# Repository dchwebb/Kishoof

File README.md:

# Kishoof

## Overview

Kishoof is a Wavetable synthesizer designed for use in a Eurorack modular system. A dual channel architecture allows simultaneous playback of two channels each offering a different range of capabilities. Wavetables are held in 64MB of internal flash storage which is exposed as a USB disk drive via a front-panel USB C connector.

Two modes of operation are available with one stepping between individual wavetable frames and one smoothly interpolating between frames. In stepped mode channel A and B can each play any of the available wavetable frames. In smooth mode Channel A plays the loaded wavetable and channel B plays an internal wavetable that can be configured to hold a range of standard waveforms and harmonics.

A warp engine allows a range of warping effects to alter channel A's signal, with Bend, Squeeze, Mirror and though-Zero Frequency Modulation from channel B available. Channel B can be modulated via addition (mixing) and multiplication (ring modulation) with channel A and its playback direction can be reversed. Dynamic anti-aliasing filters eliminate aliasing regardless of modulation settings. 

A circular TFT LCD display shows both or either channel's waveform with any warping and modulation applied. A serial console available over a USB virtual COM port allows advanced configuration, calibration and trouble-shooting facilities.

The module was designed in conjunction with musician Tal Shoshani who produced the following demonstration video:

- **[Operation Manual](Kishoof_Manual.md)**

## Technical

Kishoof is based on an STM32H7B0 microcontroller clocked at 280MHz. Internal flash storage uses a Macronix MX25LM51245G 512Mbit NOR flash IC, clocked at 76.8MHz. The flash is controlled by the MCU using OctoSPI.

A TI PCM5100APW audio DAC is used for wavetable playback, operating in stereo at 48KHz. This is interfaced to the MCU over I2S. The MCU's internal 12 bit ADCs receive potentiometer and scaled Control voltage inputs.

The display is a circular 1.28 inch 240x240 IPS TFT LCD with GC9A01 Driver and is controlled via SPI. USB is connected via a front-panel USB C connector with ESD Protection.

**Construction**

The module is constructed of four PCBs: Component board, Control board, LCD daughterboard and Front Panel. The Component board is a 4-layer board. All others are 2 layer.

Circuit Design and layout using Kicad v8:

[Components schematic](Hardware/Kishoof_Components.pdf)

[Controls schematic](Hardware/Kishoof_Controls.pdf)

**Firmware**

Firmware written in C++20 using STM32CubeIDE version 1.15.1 and is available [here](Kishoof)

## Power

Digital power is supplied through a TI TPS561201 3.3V switching power supply and analog power via a 3.3V linear regulator.

- +12V current draw: 149 mA
- -12V Current draw: 7 mA

## Hardware Errata and Potential fixes

- VCA input should be normalised to a ~7V signal (currently bodged to 3.3V).
- Improve ground return paths on LCD daughterboard
- Invert LCD daughterboard to make orientation easier, and move pads towards cutout
- Fix footprint for switched potentiometer (Warp Type)

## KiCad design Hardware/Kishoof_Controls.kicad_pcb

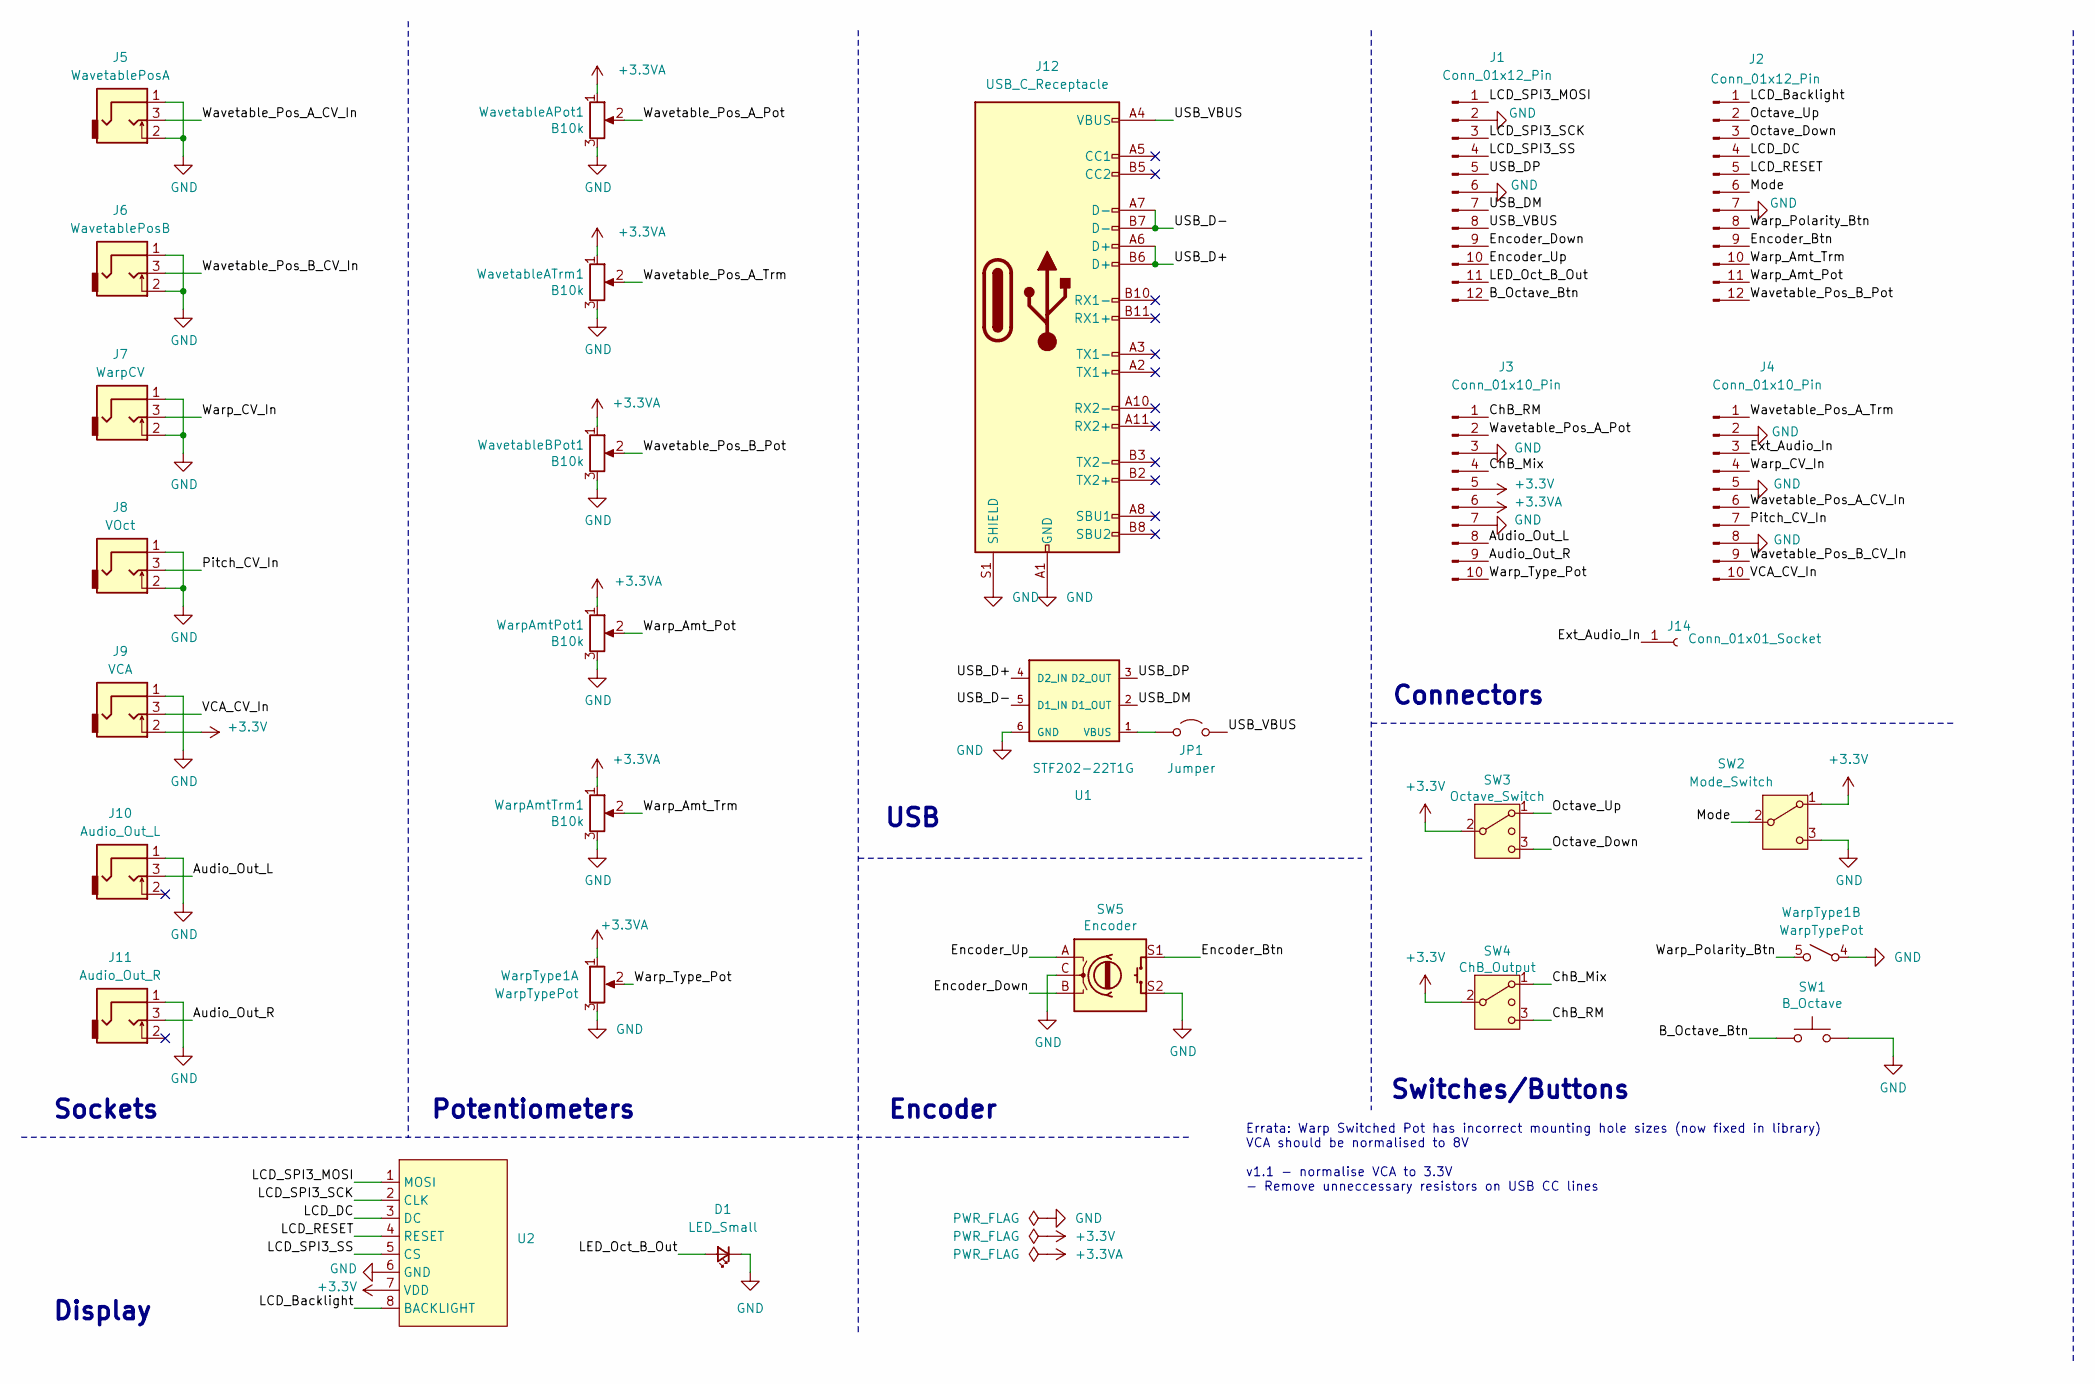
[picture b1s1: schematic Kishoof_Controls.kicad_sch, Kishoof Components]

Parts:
D1: LED_Small; LED_D3.0mm_FlatTop
J1, J2: Conn_01x12_Pin; PinSocket_1x12_P2.54mm_Vertical
J3, J4: Conn_01x10_Pin; PinSocket_1x10_P2.54mm_Vertical
J5: WavetablePosA; THONKICONN_hole
J6: WavetablePosB; THONKICONN_hole
J7: WarpCV; THONKICONN_hole
J8: VOct; THONKICONN_hole
J9: VCA; THONKICONN_hole
J10: Audio_Out_L; THONKICONN_hole
J11: Audio_Out_R; THONKICONN_hole
J12: USB_C_Receptacle; USB_C_Receptacle_Amphenol_12401951E412A
J14: Conn_01x01_Socket; PinHeader_1x01_P2.54mm_Vertical
JP1: Jumper; SolderJumper-2_P1.3mm_Open_RoundedPad1.0x1.5mm
SW1: B_Octave; SW_PUSH_6mm_aligned
SW2: Mode_Switch; SPDT_Miniature
SW3: Octave_Switch; SP3T_Mini_Switch
SW4: ChB_Output; SP3T_Mini_Switch
SW5: Encoder
U1: STF202-22T1G
U2: LCD_Riser
WarpAmtPot1: B10k; Alpha_9mm_Potentiometer_Aligned
WarpAmtTrm1: B10k; Alpha_9mm_Potentiometer_Aligned
WarpType1: WarpTypePot; Bourns_Switch_Potentiometer
WavetableAPot1: B10k; Alpha_9mm_Potentiometer_Aligned
WavetableATrm1: B10k; Alpha_9mm_Potentiometer_Aligned
WavetableBPot1: B10k; Alpha_9mm_Potentiometer_Aligned

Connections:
+3.3V: J3.5, J9.2, SW2.1 (A), SW3.2 (3), SW4.2 (3), U2.7 (VDD)
+3.3VA: J3.6, WarpAmtPot1.1, WarpAmtTrm1.1, WarpType1.1, WavetableAPot1.1, WavetableATrm1.1, WavetableBPot1.1
/Audio_Out_L: J3.8, J10.3
/Audio_Out_R: J3.9, J11.3
/B_Octave_Btn: J1.12, SW1.1
/ChB_Mix: J3.4, SW4.1
/ChB_RM: J3.1, SW4.3 (4)
/Encoder_Btn: J2.9, SW5.S1
/Encoder_Down: J1.9, SW5.B
/Encoder_Up: J1.10, SW5.A
/Ext_Audio_In: J4.3, J14.1
/LCD_Backlight: J2.1, U2.8 (BACKLIGHT)
/LCD_DC: J2.4, U2.3 (DC)
/LCD_RESET: J2.5, U2.4 (RESET)
/LCD_SPI3_MOSI: J1.1, U2.1 (MOSI)
/LCD_SPI3_SCK: J1.3, U2.2 (CLK)
/LCD_SPI3_SS: J1.4, U2.5 (CS)
/LED_Oct_B_Out: D1.2 (A), J1.11
/Mode: J2.6, SW2.2 (B)
/Octave_Down: J2.3, SW3.3 (4)
/Octave_Up: J2.2, SW3.1
/Pitch_CV_In: J4.7, J8.3
/USB_D+: J12.A6 (D+), J12.B6 (D+), U1.4 (D2_IN)
/USB_D-: J12.A7 (D-), J12.B7 (D-), U1.5 (D1_IN)
/USB_DM: J1.7, U1.2 (D1_OUT)
/USB_DP: J1.5, U1.3 (D2_OUT)
/USB_VBUS: J1.8, J12.A4 (VBUS), J12.A9 (VBUS), J12.B4 (VBUS), J12.B9 (VBUS), JP1.2 (B)
/VCA_CV_In: J4.10, J9.3
/Warp_Amt_Pot: J2.11, WarpAmtPot1.2
/Warp_Amt_Trm: J2.10, WarpAmtTrm1.2
/Warp_CV_In: J4.4, J7.3
/Warp_Polarity_Btn: J2.8, WarpType1.5 (2)
/Warp_Type_Pot: J3.10, WarpType1.2
/Wavetable_Pos_A_CV_In: J4.6, J5.3
/Wavetable_Pos_A_Pot: J3.2, WavetableAPot1.2
/Wavetable_Pos_A_Trm: J4.1, WavetableATrm1.2
/Wavetable_Pos_B_CV_In: J4.9, J6.3
/Wavetable_Pos_B_Pot: J2.12, WavetableBPot1.2
GND: D1.1 (K), J1.2, J1.6, J2.7, J3.3, J3.7, J4.2, J4.5, J4.8, J5.1, J5.2, J6.1, J6.2, J7.1, J7.2, J8.1, J8.2, J9.1, J10.1, J11.1, J12.A1 (GND), J12.A12 (GND), J12.B1 (GND), J12.B12 (GND), J12.S1 (SHIELD), SW1.2, SW2.3 (C), SW5.C, SW5.S2, U1.6 (GND), U2.6 (GND), WarpAmtPot1.3, WarpAmtTrm1.3, WarpType1.3, WarpType1.4 (1), WavetableAPot1.3, WavetableATrm1.3, WavetableBPot1.3
unnamed: JP1.1 (A), U1.1 (VBUS)

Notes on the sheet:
Encoder
Errata: Warp Switched Pot has incorrect mounting hole sizes (now fixed in library) VCA should be normalised to 8V v1.1 - normalise VCA to 3.3V - Remove unneccessary resistors on USB CC lines
Sockets
Connectors
Potentiometers
Switches/Buttons
Display
USB

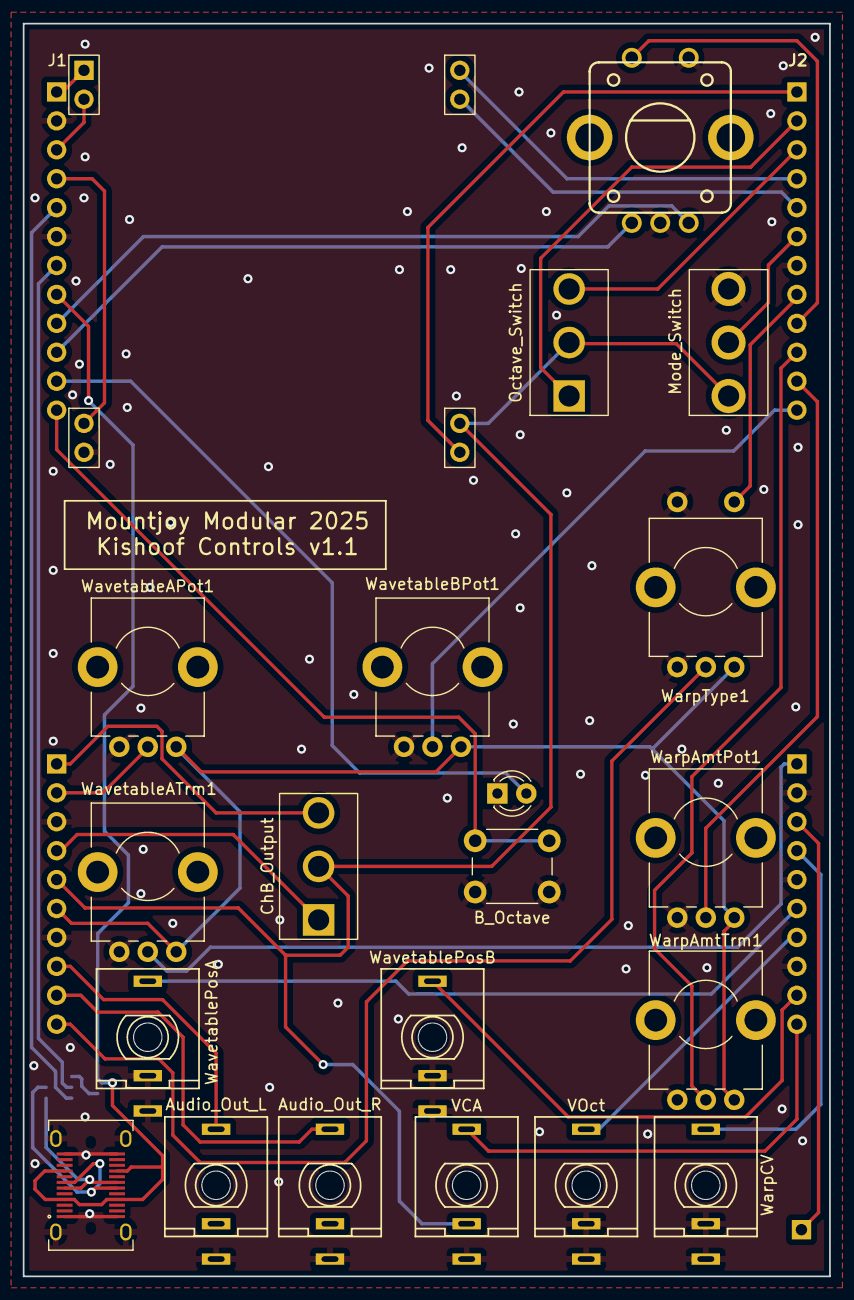
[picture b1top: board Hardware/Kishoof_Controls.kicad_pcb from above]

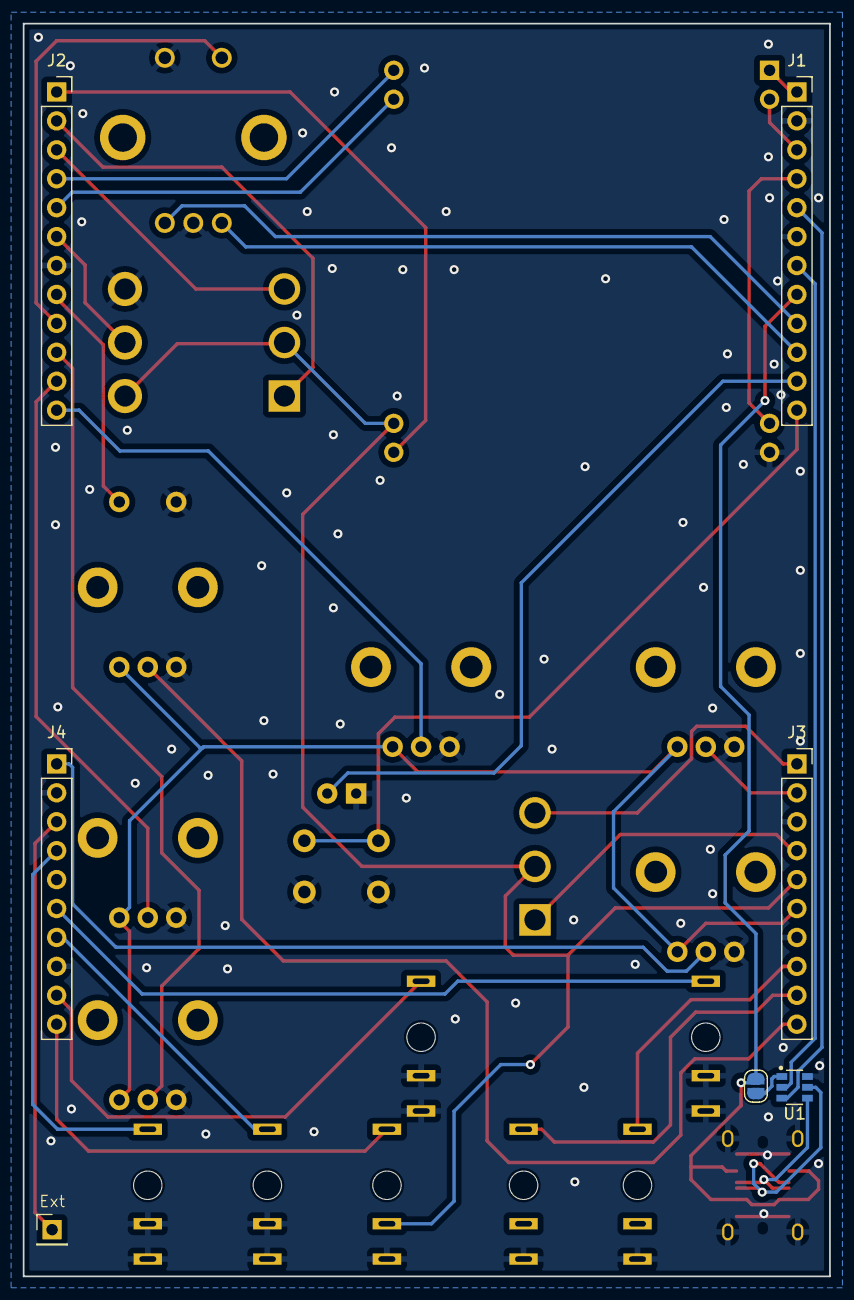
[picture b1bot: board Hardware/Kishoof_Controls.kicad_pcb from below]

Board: 2 copper layers, 70.8 x 110.0 mm, 28 parts (7 on the bottom side), 40 nets.

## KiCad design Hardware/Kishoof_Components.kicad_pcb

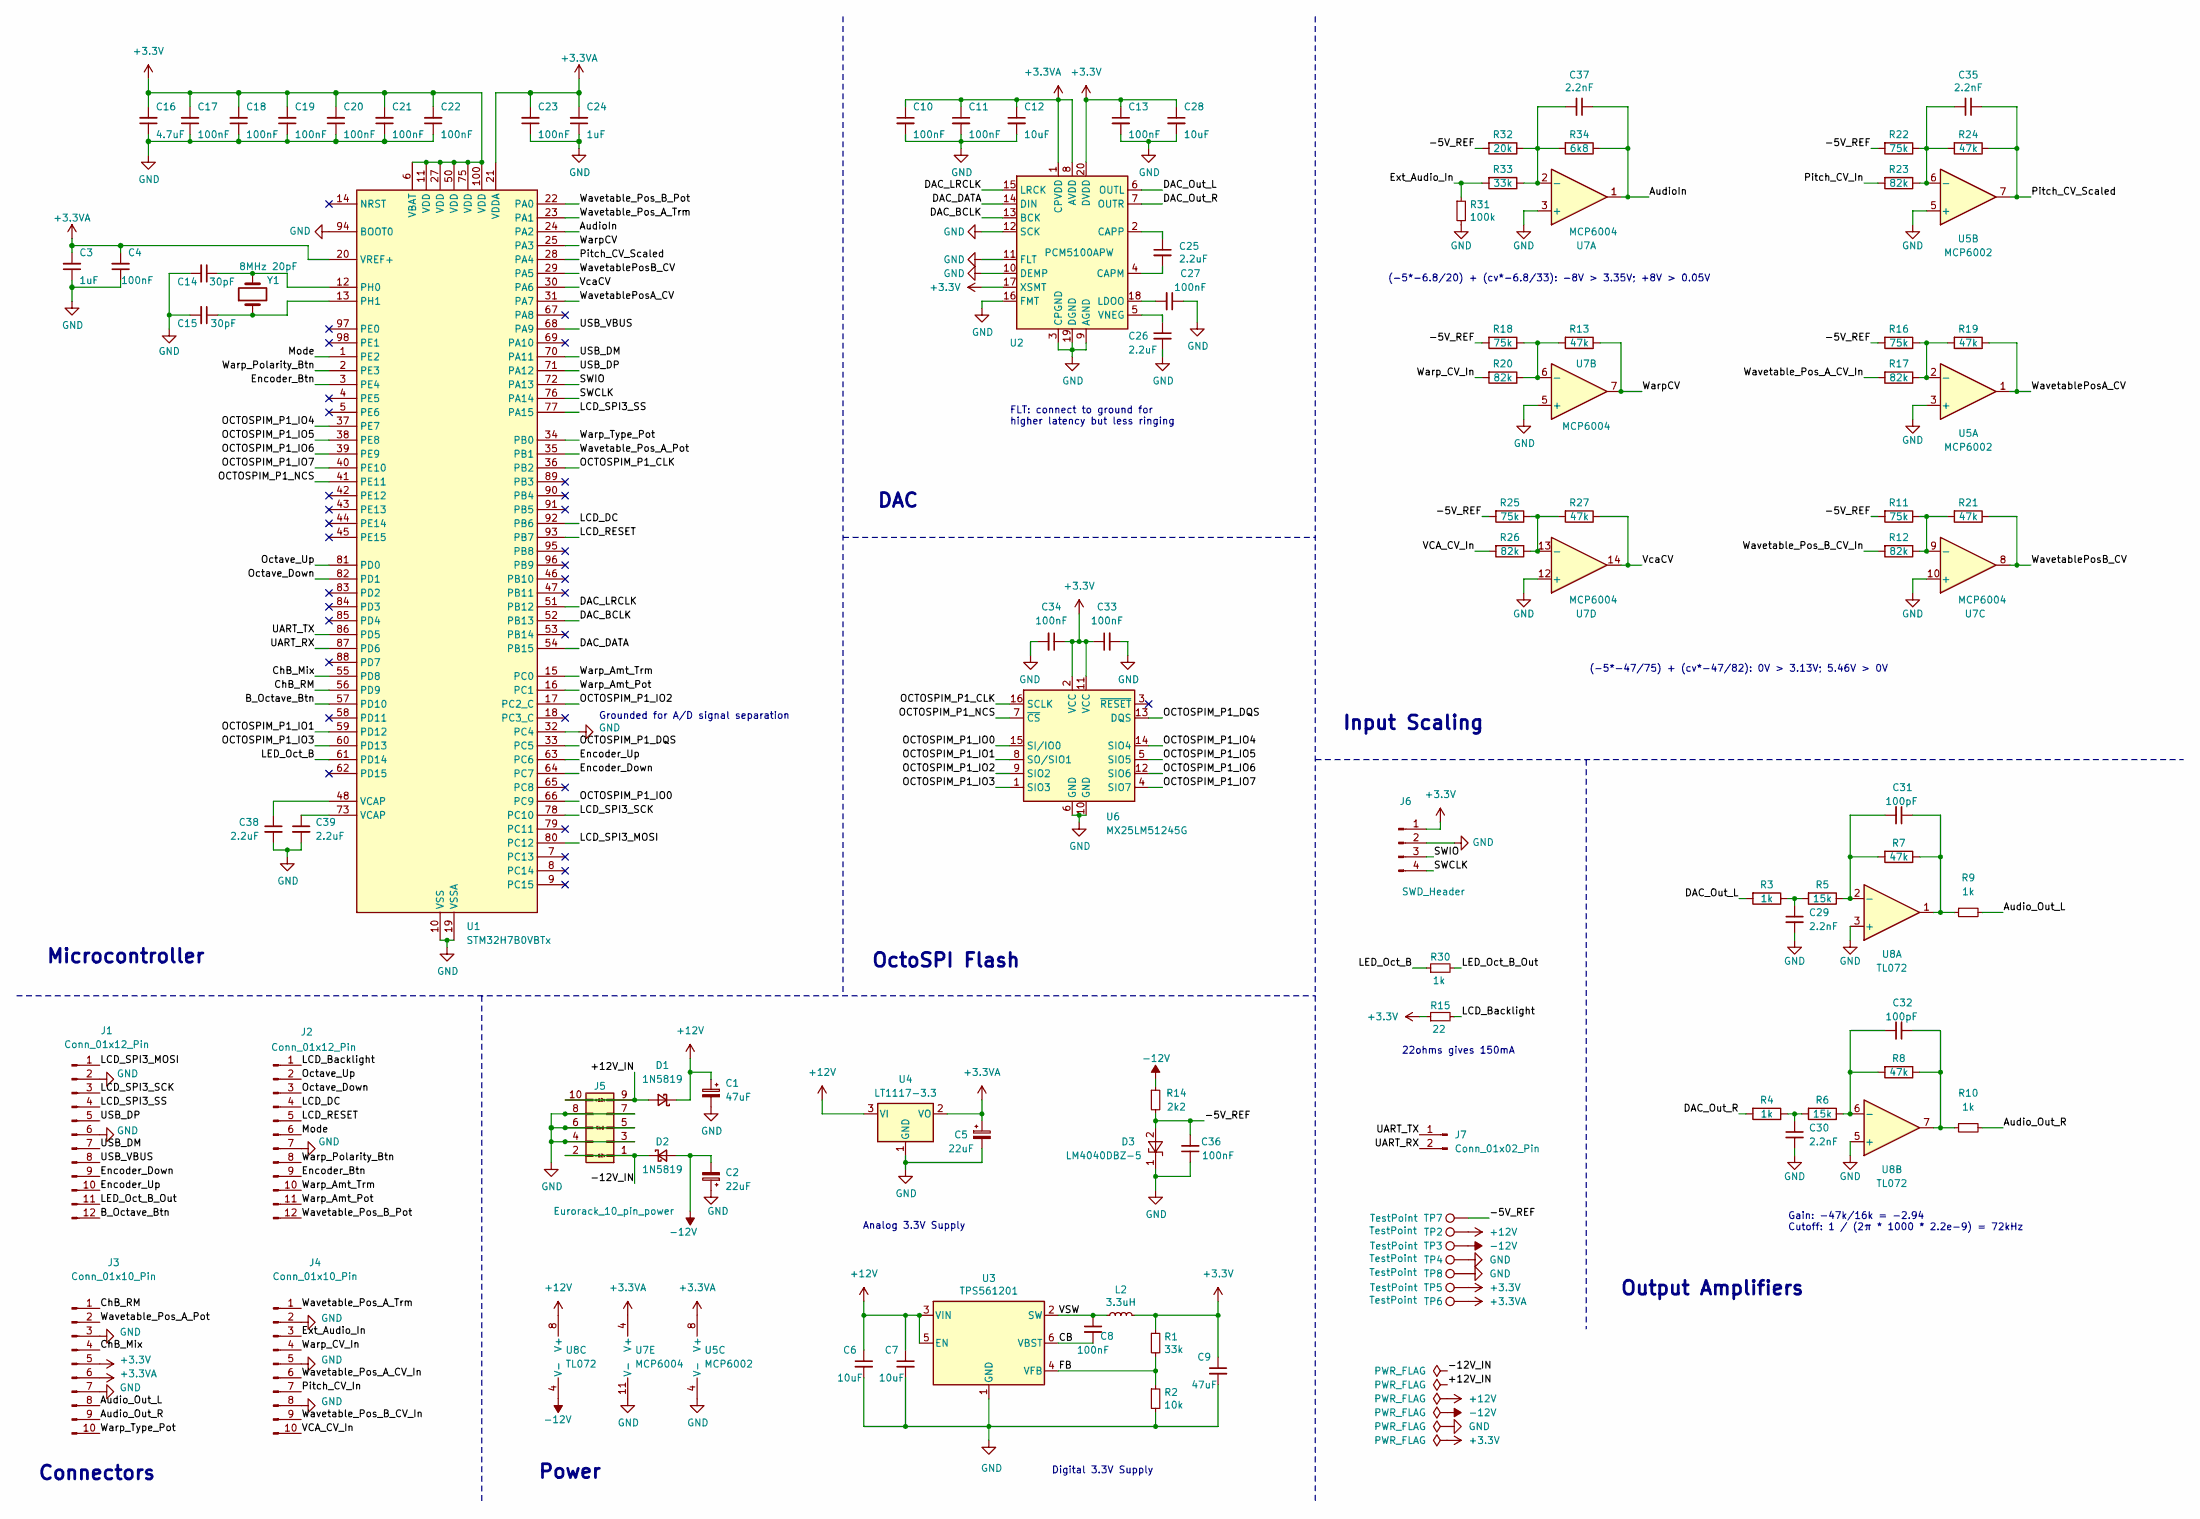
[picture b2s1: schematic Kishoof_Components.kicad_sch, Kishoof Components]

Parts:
C1: 47uF; CP_Elec_4x5.8
C2: 22uF; CP_Elec_4x5.8
C3, C24: 1uF; C_0603_1608Metric; Part_Number C15849
C4, C8, C10, C11, C13, C17, C18, C19, C20, C21, C22, C27, C33, C34, C36: 100nF; C_0603_1608Metric; Part_Number C14663
C5: 22uF; CP_Elec_4x5.8; Part_Number C134793
C6, C7: 10uF; C_0805_2012Metric; Part_Number C57112
C9: 47uF; C_1206_3216Metric; Part_Number C57112
C12, C28: 10uF; C_0603_1608Metric; Part_Number C15850
C14, C15: 30pF; C_0603_1608Metric; Part_Number C22397
C16: 4.7uF; C_0603_1608Metric; Part_Number C19666
C23: 100nF; C_0603_1608Metric; Part_Number C57112
C25, C26, C38, C39: 2.2uF; C_0603_1608Metric; Part_Number C23630
C29, C30, C35, C37: 2.2nF; C_0603_1608Metric; Part_Number C1604
C31, C32: 100pF; C_0603_1608Metric; Part_Number C14858
D1, D2: 1N5819; D_SOD-123; Part_Number C8598
D3: LM4040DBZ-5; SOT-23; Part_Number C156291
J1, J2: Conn_01x12_Pin; PinHeader_1x12_P2.54mm_Vertical
J3, J4: Conn_01x10_Pin; PinHeader_1x10_P2.54mm_Vertical
J5: Eurorack_10_pin_power; Eurorack_10_pin_header
J6: SWD_Header; SWD_header
J7: Conn_01x02_Pin; PinHeader_1x02_P2.54mm_Vertical
L2: 3.3uH; L_0806
R1, R33: 33k; R_0603_1608Metric; Part_Number C25819
R2: 10k; R_0603_1608Metric; Part_Number C25804
R3, R4, R9, R10, R30: 1k; R_0603_1608Metric; Part_Number C4190
R5, R6: 15k; R_0603_1608Metric; Part_Number C25804
R7, R8, R13, R19, R21, R24, R27: 47k; R_0603_1608Metric; Part_Number C25819
R11, R16, R18, R22, R25: 75k; R_0603_1608Metric; Part_Number C23242
R12, R17, R20, R23, R26: 82k; R_0603_1608Metric; Part_Number C23265
R14: 2k2; R_0603_1608Metric; Part_Number C4190
R15: 22; R_0603_1608Metric; Part_Number C23345
R31: 100k; R_0603_1608Metric; Part_Number C25803
R32: 20k; R_0603_1608Metric; Part_Number C4184
R34: 6k8; R_0603_1608Metric; Part_Number C23212
TP2, TP3, TP4, TP5, TP6, TP7, TP8: TestPoint; 1.3mm_Test_Point
U1: STM32H7B0VBTx; LQFP-100_14x14mm_P0.5mm
U2: PCM5100APW; TSSOP-20_4.4x6.5mm_P0.65mm
U3: TPS561201; TSOT-23-6_HandSoldering
U4: LT1117-3.3; SOT-223-3_TabPin2
U5: MCP6002; SOIC-8_3.9x4.9mm_P1.27mm
U6: MX25LM51245G; SOIC-16W_7.5x10.3mm_P1.27mm
U7: MCP6004; SO-14_3.9x8.65mm_P1.27mm
U8: TL072; SOIC-8_3.9x4.9mm_P1.27mm; Part_Number C6961
Y1: 8MHz 20pF; Crystal_SMD_Abracon_ABM3-2Pin_5.0x3.2mm; Part_Number C115962

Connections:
+3.3V: C9.1, C13.1, C16.2, C17.2, C18.2, C19.2, C20.2, C21.2, C22.2, C28.1, C33.1, C34.1, J3.5, J6.1, L2.2, R1.1, R15.1, TP5.1, U1.6 (VBAT), U1.11 (VDD), U1.27 (VDD), U1.50 (VDD), U1.75 (VDD), U1.100 (VDD), U2.17 (XSMT), U2.20 (DVDD), U6.2 (VCC), U6.11 (VCC)
+3.3VA: C3.2, C4.2, C5.1, C10.1, C11.1, C12.1, C23.2, C24.2, J3.6, TP6.1, U1.20 (VREF+), U1.21 (VDDA), U2.1 (CPVDD), U2.8 (AVDD), U4.2 (VO), U5.8 (V+), U7.4 (V+)
+12V: C1.1, C6.1, C7.1, D1.1 (K), TP2.1, U3.3 (VIN), U3.5 (EN), U4.3 (VI), U8.8 (V+)
-12V: C2.2, D2.2 (A), R14.1, TP3.1, U8.4 (V-)
/+12V_IN: D1.2 (A), J5.9, J5.10
/-5V_REF: C36.2, D3.2 (A), R11.2, R14.2, R16.2, R18.2, R22.2, R25.2, R32.2, TP7.1
/-12V_IN: D2.1 (K), J5.1, J5.2
/AudioIn: C37.1, R34.1, U1.24 (PA2), U7.1
/Audio_Out_L: J3.8, R9.2
/Audio_Out_R: J3.9, R10.2
/B_Octave_Btn: J1.12, U1.57 (PD10)
/CB: C8.2, U3.6 (VBST)
/ChB_Mix: J3.4, U1.55 (PD8)
/ChB_RM: J3.1, U1.56 (PD9)
/DAC_BCLK: U1.52 (PB13), U2.13 (BCK)
/DAC_DATA: U1.54 (PB15), U2.14 (DIN)
/DAC_LRCLK: U1.51 (PB12), U2.15 (LRCK)
/DAC_Out_L: R3.2, U2.6 (OUTL)
/DAC_Out_R: R4.2, U2.7 (OUTR)
/Encoder_Btn: J2.9, U1.3 (PE4)
/Encoder_Down: J1.9, U1.64 (PC7)
/Encoder_Up: J1.10, U1.63 (PC6)
/Ext_Audio_In: J4.3, R31.1, R33.2
/FB: R1.2, R2.1, U3.4 (VFB)
/LCD_Backlight: J2.1, R15.2
/LCD_DC: J2.4, U1.92 (PB6)
/LCD_RESET: J2.5, U1.93 (PB7)
/LCD_SPI3_MOSI: J1.1, U1.80 (PC12)
/LCD_SPI3_SCK: J1.3, U1.78 (PC10)
/LCD_SPI3_SS: J1.4, U1.77 (PA15)
/LED_Oct_B: R30.1, U1.61 (PD14)
/LED_Oct_B_Out: J1.11, R30.2
/Mode: J2.6, U1.1 (PE2)
/OCTOSPIM_P1_CLK: U1.36 (PB2), U6.16 (SCLK)
/OCTOSPIM_P1_DQS: U1.33 (PC5), U6.13 (DQS)
/OCTOSPIM_P1_IO0: U1.66 (PC9), U6.15 (SI/IO0)
/OCTOSPIM_P1_IO1: U1.59 (PD12), U6.8 (SO/SIO1)
/OCTOSPIM_P1_IO2: U1.17 (PC2_C), U6.9 (SIO2)
/OCTOSPIM_P1_IO3: U1.60 (PD13), U6.1 (SIO3)
/OCTOSPIM_P1_IO4: U1.37 (PE7), U6.14 (SIO4)
/OCTOSPIM_P1_IO5: U1.38 (PE8), U6.5 (SIO5)
/OCTOSPIM_P1_IO6: U1.39 (PE9), U6.12 (SIO6)
/OCTOSPIM_P1_IO7: U1.40 (PE10), U6.4 (SIO7)
/OCTOSPIM_P1_NCS: U1.41 (PE11), U6.7 (~CS)
/Octave_Down: J2.3, U1.82 (PD1)
/Octave_Up: J2.2, U1.81 (PD0)
/Pitch_CV_In: J4.7, R23.2
/Pitch_CV_Scaled: C35.1, R24.1, U1.28 (PA4), U5.7
/SWCLK: J6.4, U1.76 (PA14)
/SWIO: J6.3, U1.72 (PA13)
/UART_RX: J7.2, U1.87 (PD6)
/UART_TX: J7.1, U1.86 (PD5)
/USB_DM: J1.7, U1.70 (PA11)
/USB_DP: J1.5, U1.71 (PA12)
/USB_VBUS: J1.8, U1.68 (PA9)
/VCA_CV_In: J4.10, R26.2
/VSW: C8.1, L2.1, U3.2 (SW)
/VcaCV: R27.1, U1.30 (PA6), U7.14
/WarpCV: R13.1, U1.25 (PA3), U7.7
/Warp_Amt_Pot: J2.11, U1.16 (PC1)
/Warp_Amt_Trm: J2.10, U1.15 (PC0)
/Warp_CV_In: J4.4, R20.2
/Warp_Polarity_Btn: J2.8, U1.2 (PE3)
/Warp_Type_Pot: J3.10, U1.34 (PB0)
/WavetablePosA_CV: R19.1, U1.31 (PA7), U5.1
/WavetablePosB_CV: R21.1, U1.29 (PA5), U7.8
/Wavetable_Pos_A_CV_In: J4.6, R17.2
/Wavetable_Pos_A_Pot: J3.2, U1.35 (PB1)
/Wavetable_Pos_A_Trm: J4.1, U1.23 (PA1)
/Wavetable_Pos_B_CV_In: J4.9, R12.2
/Wavetable_Pos_B_Pot: J2.12, U1.22 (PA0)
GND: C1.2, C2.1, C3.1, C4.1, C5.2, C6.2, C7.2, C9.2, C10.2, C11.2, C12.2, C13.2, C14.2, C15.2, C16.1, C17.1, C18.1, C19.1, C20.1, C21.1, C22.1, C23.1, C24.1, C26.2, C27.1, C28.2, C29.2, C30.2, C33.2, C34.2, C36.1, C38.2, C39.2, D3.1 (K), J1.2, J1.6, J2.7, J3.3, J3.7, J4.2, J4.5, J4.8, J5.3, J5.4, J5.5, J5.6, J5.7, J5.8, J6.2, R2.2, R31.2, TP4.1, TP8.1, U1.10 (VSS), U1.19 (VSSA), U1.26 (VSS), U1.32 (PC4), U1.49 (VSS), U1.74 (VSS), U1.94 (BOOT0), U1.99 (VSS), U2.3 (CPGND), U2.9 (AGND), U2.10 (DEMP), U2.11 (FLT), U2.12 (SCK), U2.16 (FMT), U2.19 (DGND), U3.1 (GND), U4.1 (GND), U5.3 (+), U5.4 (V-), U5.5 (+), U6.6 (GND), U6.10 (GND), U7.3 (+), U7.5 (+), U7.10 (+), U7.11 (V-), U7.12 (+), U8.3 (+), U8.5 (+)
unnamed: C29.1, R3.1, R5.2
unnamed: C30.1, R4.1, R6.2
unnamed: C31.1, R7.1, R9.1, U8.1
unnamed: C32.1, R8.1, R10.1, U8.7
unnamed: C38.1, U1.48 (VCAP)
unnamed: C39.1, U1.73 (VCAP)
unnamed: C14.1, U1.12 (PH0), Y1.2
unnamed: C15.1, U1.13 (PH1), Y1.1
unnamed: C25.2, U2.4 (CAPM)
unnamed: C25.1, U2.2 (CAPP)
unnamed: C27.2, U2.18 (LDOO)
unnamed: C26.1, U2.5 (VNEG)
unnamed: R16.1, R17.1, R19.2, U5.2 (-)
unnamed: C35.2, R22.1, R23.1, R24.2, U5.6 (-)
unnamed: C37.2, R32.1, R33.1, R34.2, U7.2 (-)
unnamed: R13.2, R18.1, R20.1, U7.6 (-)
unnamed: R11.1, R12.1, R21.2, U7.9 (-)
unnamed: R25.1, R26.1, R27.2, U7.13 (-)
unnamed: C31.2, R5.1, R7.2, U8.2 (-)
unnamed: C32.2, R6.1, R8.2, U8.6 (-)

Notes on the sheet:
DAC
Gain: -47k/16k = -2.94 Cutoff: 1 / (2π * 1000 * 2.2e-9) = 72kHz
Connectors
FLT: connect to ground for higher latency but less ringing
Digital 3.3V Supply
(-5*-47/75) + (cv*-47/82): 0V > 3.13V; 5.46V > 0V
OctoSPI Flash
Input Scaling
Output Amplifiers
Grounded for A/D signal separation
Power
Analog 3.3V Supply
Microcontroller
22ohms gives 150mA
(-5*-6.8/20) + (cv*-6.8/33): -8V > 3.35V; +8V > 0.05V

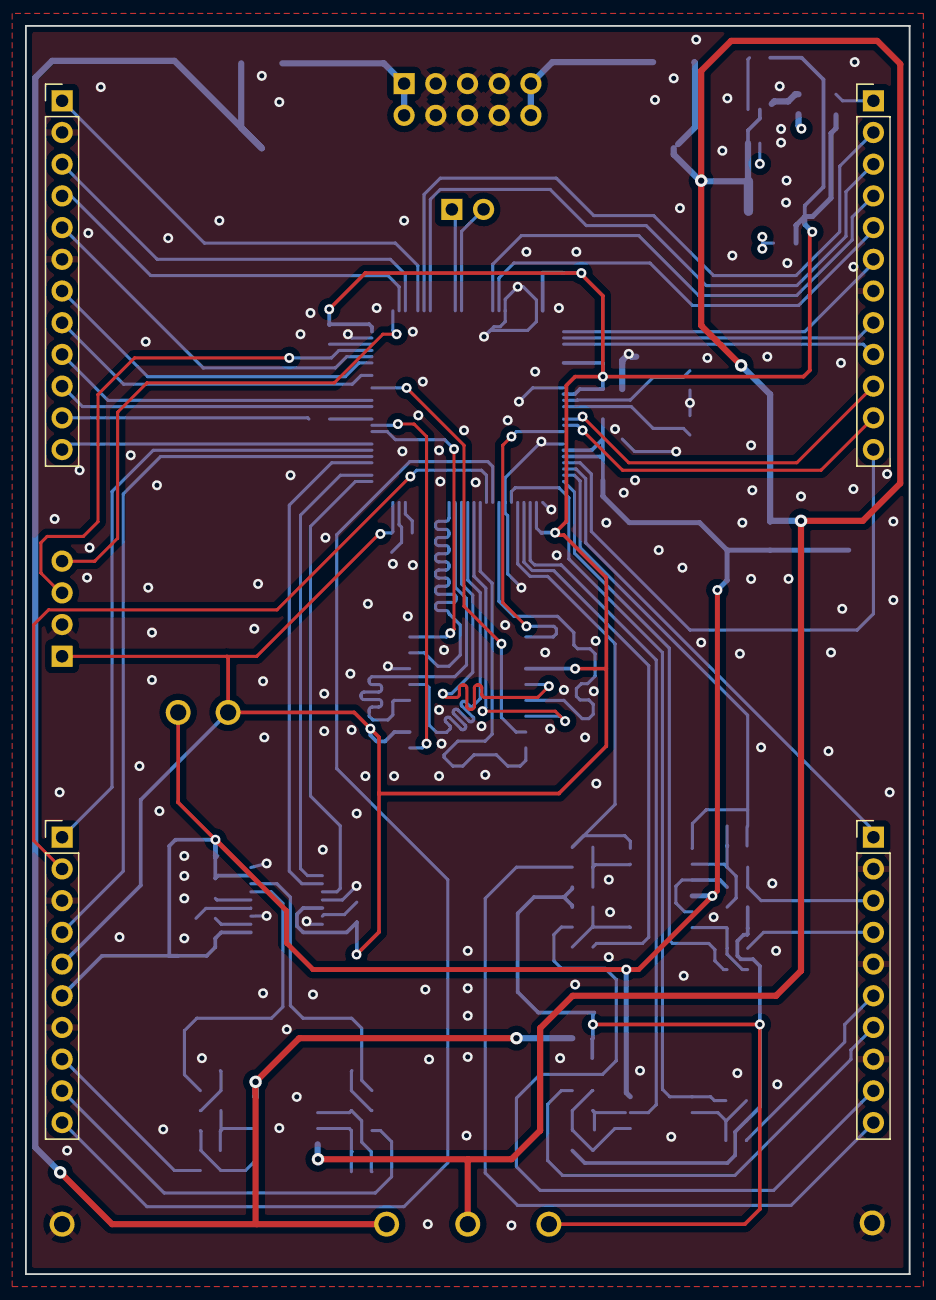
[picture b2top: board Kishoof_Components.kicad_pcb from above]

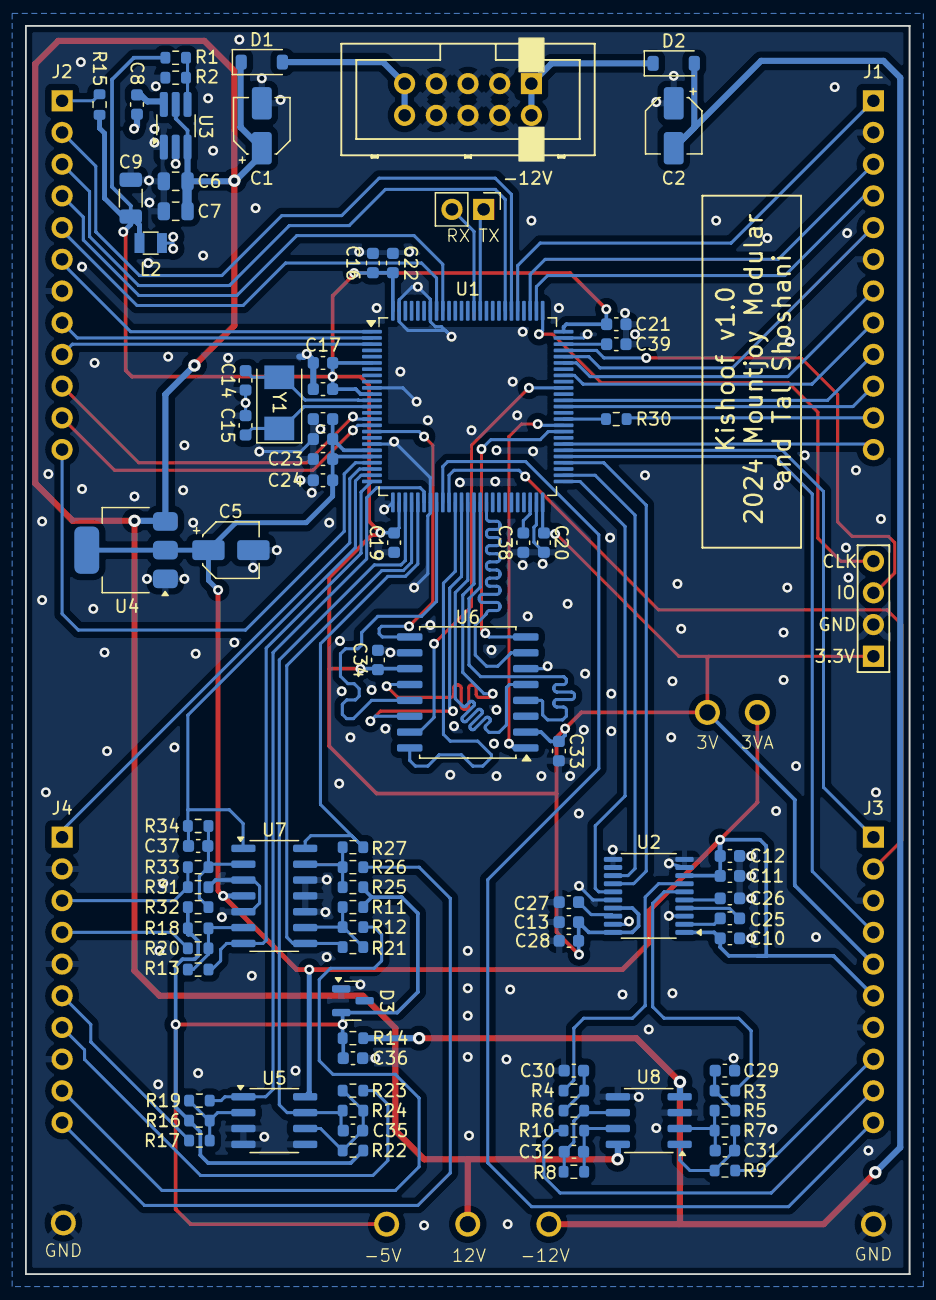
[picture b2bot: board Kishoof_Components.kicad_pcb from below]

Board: 4 copper layers, 70.8 x 100.0 mm, 98 parts (94 on the bottom side), 92 nets.

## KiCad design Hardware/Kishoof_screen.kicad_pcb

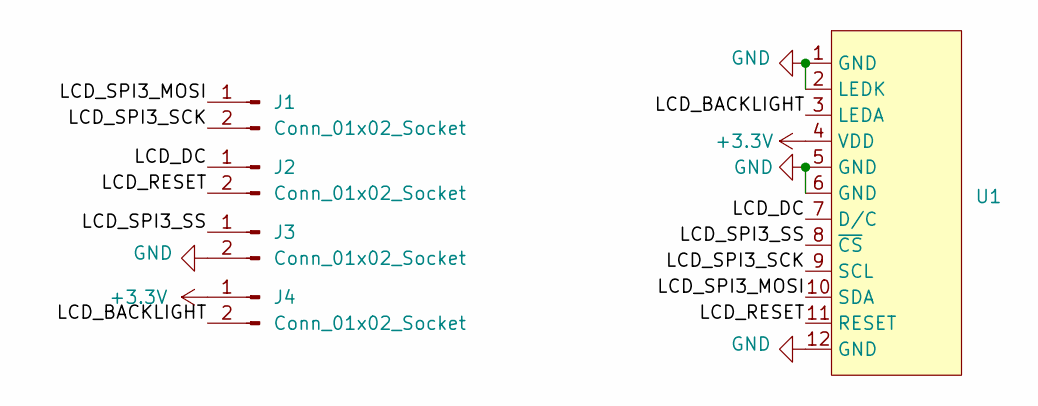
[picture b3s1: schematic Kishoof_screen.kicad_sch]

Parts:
J1, J2, J3, J4: Conn_01x02_Socket; PinHeader_1x02_P2.54mm_Vertical
U1: Round_LCD

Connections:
+3.3V: J4.1, U1.4 (VDD)
/LCD_BACKLIGHT: J4.2, U1.3 (LEDA)
/LCD_DC: J2.1, U1.7 (D/C)
/LCD_RESET: J2.2, U1.11 (RESET)
/LCD_SPI3_MOSI: J1.1, U1.10 (SDA)
/LCD_SPI3_SCK: J1.2, U1.9 (SCL)
/LCD_SPI3_SS: J3.1, U1.8 (~CS)
GND: J3.2, U1.1 (GND), U1.2 (LEDK), U1.5 (GND), U1.6 (GND), U1.12 (GND)

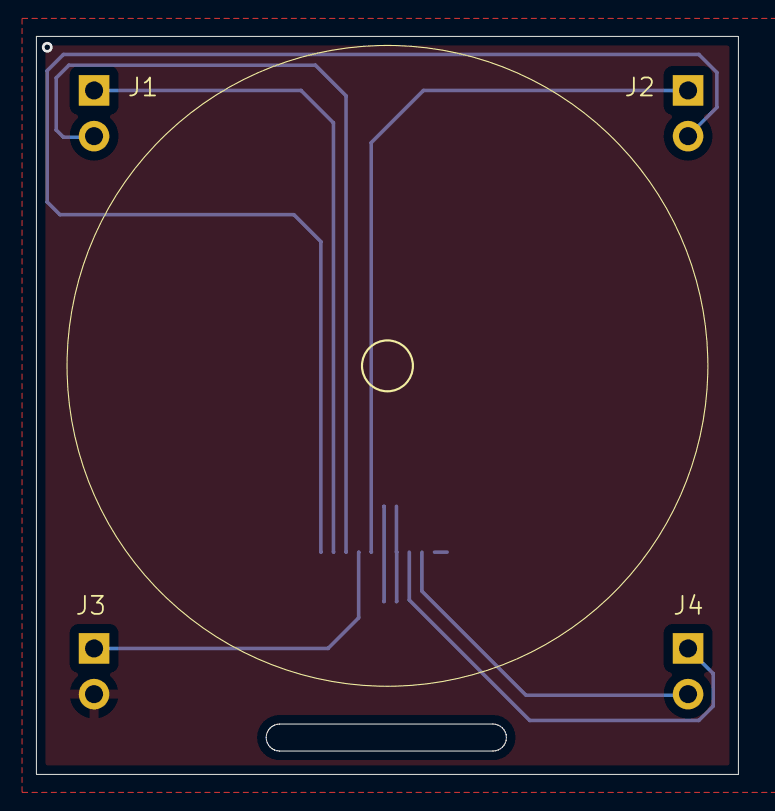
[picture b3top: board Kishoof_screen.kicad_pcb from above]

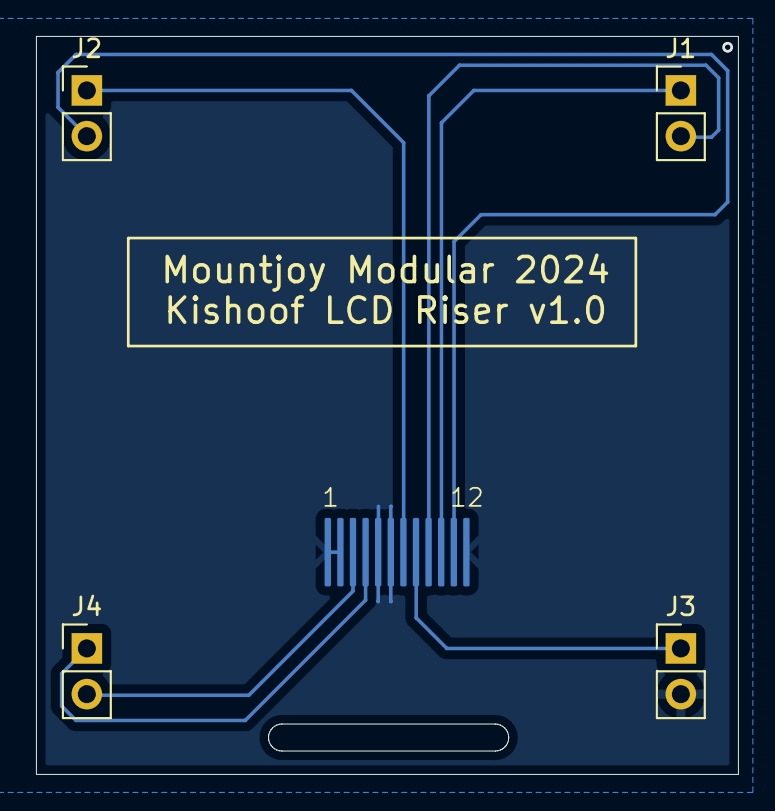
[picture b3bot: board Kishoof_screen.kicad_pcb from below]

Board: 2 copper layers, 39.0 x 41.0 mm, 5 parts (5 on the bottom side), 8 nets.
